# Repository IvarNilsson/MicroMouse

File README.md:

# MicroMouse

Motors and wheels:

Motorcontroller curcuit?

Motor electrokit:
[motor 1](ttps://www.electrokit.com/produkt/dc-motor-med-kuggvaxel-12vdc-301-900rpm-med-enkoder)
[Wheels 1](ttps://www.banggood.com/4PCS-SG-1603-1604-UDIRC-1601-RC-Car-Spare-Tires-Wheels-1603-005-B-Vehicles-Model-Parts-p-1832852.html?utm_source=googleshopping&utm_medium=cpc_organic&gmcCountry=SE&utm_content=minha&utm_campaign=aceng-pmax-se-en-pc&currency=SEK&cur_warehouse=CN&createTmp=1&utm_source=googleshopping&utm_medium=cpc_pt&utm_content=meruem&utm_campaign=aceng-pmax-se-all-en-220402-meruem&ad_id=&gclid=Cj0KCQjw4bipBhCyARIsAFsieCzhoUDw4CZ-vSHbWPWbA6zzIRrXuiuE_EPyn2XLgKM-56ahdmfMtzMaAotqEALw_wc)

Links:
[Tutorial](https://micromouseguideforbeginners.wordpress.com/3-part-1-motorswheels-2/)
[Pololu stuff](https://www.pololu.com/product/3081)
[Pololu stuff](https://www.pololu.com/product/713)
[wheels example](https://micromouseonline.com/2012/05/24/printed-wheels-complete-decimus-mechanicals/)
[cool ideal motor](https://www.glockenankermotor.com/en/dc-micromotors-faulhaber/1717...sr-faulhaber/328/faulhaber-motor-1717t006sr)
[Wheels 2](https://www.banggood.com/4PCS-SG-1603-1604-UDIRC-1601-RC-Car-Spare-Tires-Wheels-1603-005-A-Vehicles-Model-Parts-p-1832874.html?utm_source=googleshopping&utm_medium=cpc_pt&gmcCountry=SE&utm_content=meruem&utm_campaign=aceng-pmax-se-all-en-220402-meruem&currency=SEK&cur_warehouse=CN&createTmp=1&ad_id)

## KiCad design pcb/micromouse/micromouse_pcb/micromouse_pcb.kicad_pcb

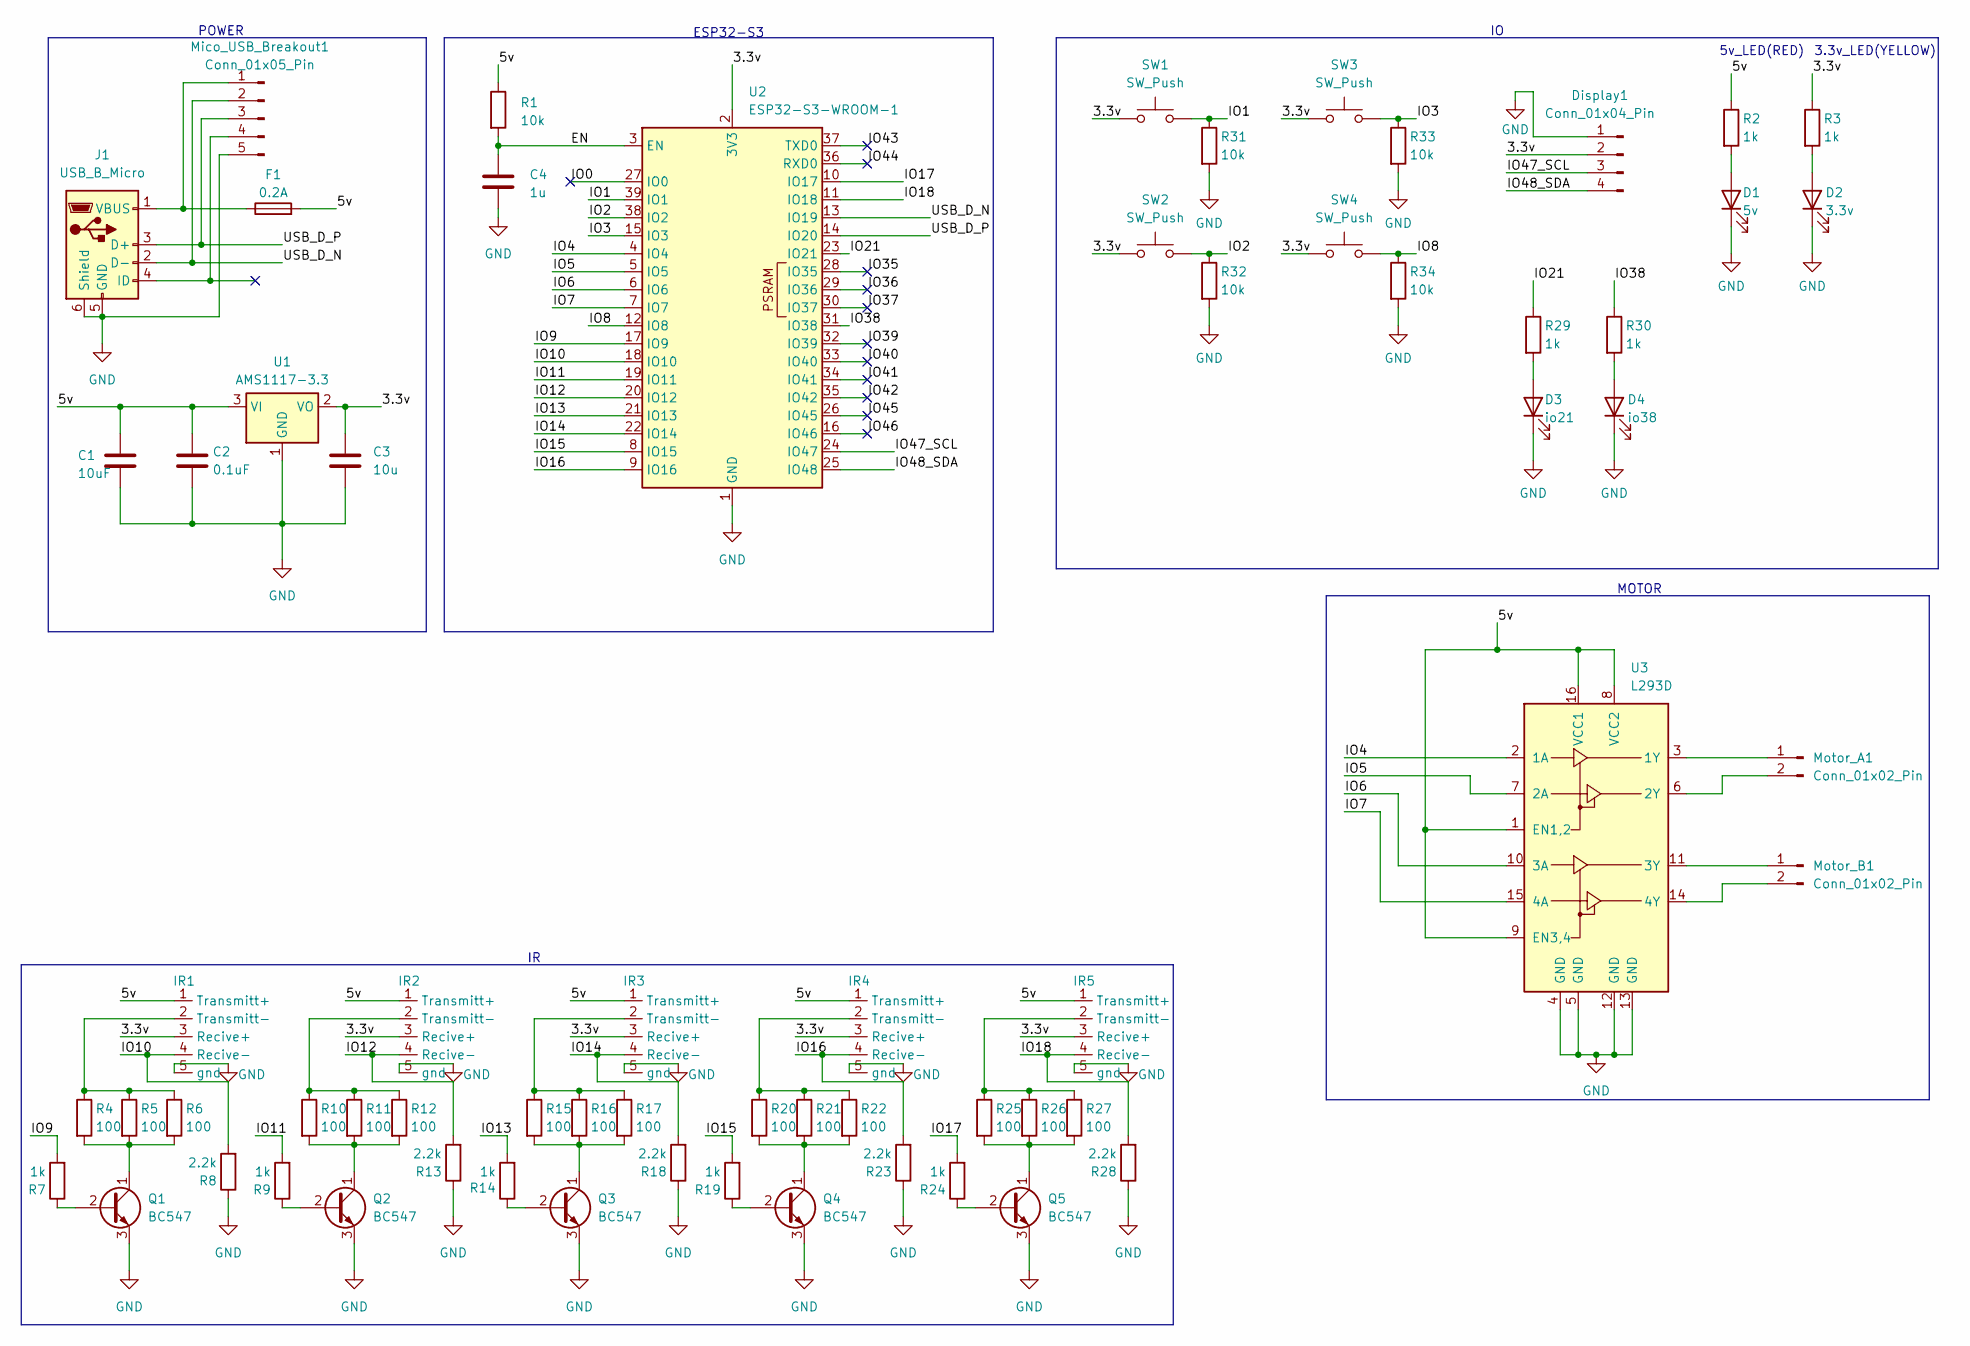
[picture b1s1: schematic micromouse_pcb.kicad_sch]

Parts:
C1: 10uF; IVAR_1206_SMD_C
C2: 0.1uF; IVAR_1206_SMD_C
C3: 10u; IVAR_1206_SMD_C
C4: 1u; IVAR_1206_SMD_C
D1: 5v; IVAR_0603_SMD_LED
D2: 3.3v; IVAR_0603_SMD_LED
D3: io21; IVAR_0603_SMD_LED
D4: io38; IVAR_0603_SMD_LED
Display1: Conn_01x04_Pin; IVAR_OLED_I2C
F1: 0.2A; IVAR_1206_SMD_FUSE
IR1, IR2, IR3, IR4, IR5: IVAR_IR
J1: USB_B_Micro; USB_Micro-B_Amphenol_10103594-0001LF_Horizontal
Mico_USB_Breakout1: Conn_01x05_Pin; IVAR_Micro_USB_breakout_board_5pin
Motor_A1: Conn_01x02_Pin; PinHeader_1x02_P2.54mm_Vertical
Motor_B1: Conn_01x02_Pin; PinHeader_1x02_P2.54mm_Vertical
Q1, Q2, Q3, Q4, Q5: BC547; TO-92_Inline
R1, R31, R32, R33, R34: 10k; IVAR_1206_SMD_R
R2, R3, R7, R9, R14, R19, R24, R29, R30: 1k; IVAR_1206_SMD_R
R4, R5, R6, R10, R11, R12, R15, R16, R17, R20, R21, R22, R25, R26, R27: 100; IVAR_1206_SMD_R
R8, R13, R18, R23, R28: 2.2k; IVAR_1206_SMD_R
SW1, SW2, SW3, SW4: SW_Push; IVAR_BUTTON_RED_SMD
U1: AMS1117-3.3; SOT-223-3_TabPin2
U2: ESP32-S3-WROOM-1
U3: L293D; DIP-16_W7.62mm

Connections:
/3.3v: C3.1, Display1.2, IR1.3 (Recive+), IR2.3 (Recive+), IR3.3 (Recive+), IR4.3 (Recive+), IR5.3 (Recive+), R3.1, SW1.1, SW2.1, SW3.1, SW4.1, U1.2 (VO), U2.2 (3V3)
/5v: C1.1, C2.1, F1.2, IR1.1 (Transmitt+), IR2.1 (Transmitt+), IR3.1 (Transmitt+), IR4.1 (Transmitt+), IR5.1 (Transmitt+), R1.1, R2.1, U1.3 (VI), U3.1 (EN1,2), U3.8 (VCC2), U3.9 (EN3,4), U3.16 (VCC1)
/EN: C4.1, R1.2, U2.3 (EN)
/IO0: U2.27 (IO0)
/IO1: R31.1, SW1.2, U2.39 (IO1)
/IO2: R32.1, SW2.2, U2.38 (IO2)
/IO3: R33.1, SW3.2, U2.15 (IO3)
/IO4: U2.4 (IO4), U3.2 (1A)
/IO5: U2.5 (IO5), U3.7 (2A)
/IO6: U2.6 (IO6), U3.10 (3A)
/IO7: U2.7 (IO7), U3.15 (4A)
/IO8: R34.1, SW4.2, U2.12 (IO8)
/IO9: R7.2, U2.17 (IO9)
/IO10: IR1.4 (Recive-), R8.2, U2.18 (IO10)
/IO11: R9.2, U2.19 (IO11)
/IO12: IR2.4 (Recive-), R13.2, U2.20 (IO12)
/IO13: R14.2, U2.21 (IO13)
/IO14: IR3.4 (Recive-), R18.2, U2.22 (IO14)
/IO15: R19.2, U2.8 (IO15)
/IO16: IR4.4 (Recive-), R23.2, U2.9 (IO16)
/IO17: R24.2, U2.10 (IO17)
/IO18: IR5.4 (Recive-), R28.2, U2.11 (IO18)
/IO21: R29.1, U2.23 (IO21)
/IO35: U2.28 (IO35)
/IO36: U2.29 (IO36)
/IO37: U2.30 (IO37)
/IO38: R30.1, U2.31 (IO38)
/IO39: U2.32 (IO39)
/IO40: U2.33 (IO40)
/IO41: U2.34 (IO41)
/IO42: U2.35 (IO42)
/IO43: U2.37 (TXD0)
/IO44: U2.36 (RXD0)
/IO45: U2.26 (IO45)
/IO46: U2.16 (IO46)
/IO47_SCL: Display1.3, U2.24 (IO47)
/IO48_SDA: Display1.4, U2.25 (IO48)
/USB_D_N: J1.2 (D-), Mico_USB_Breakout1.2, U2.13 (IO19)
/USB_D_P: J1.3 (D+), Mico_USB_Breakout1.3, U2.14 (IO20)
GND: C1.2, C2.2, C3.2, C4.2, D1.1 (K), D2.1 (K), D3.1 (K), D4.1 (K), Display1.1, IR1.5 (gnd), IR2.5 (gnd), IR3.5 (gnd), IR4.5 (gnd), IR5.5 (gnd), J1.5 (GND), J1.6 (Shield), Mico_USB_Breakout1.5, Q1.3 (E), Q2.3 (E), Q3.3 (E), Q4.3 (E), Q5.3 (E), R8.1, R13.1, R18.1, R23.1, R28.1, R31.2, R32.2, R33.2, R34.2, U1.1 (GND), U2.1 (GND), U2.40 (GND), U2.41 (GND), U3.4 (GND), U3.5 (GND), U3.12 (GND), U3.13 (GND)
unnamed: D1.2 (A), R2.2
unnamed: D2.2 (A), R3.2
unnamed: D3.2 (A), R29.2
unnamed: D4.2 (A), R30.2
unnamed: IR1.2 (Transmitt-), R4.1, R5.1, R6.1
unnamed: IR2.2 (Transmitt-), R10.1, R11.1, R12.1
unnamed: IR3.2 (Transmitt-), R15.1, R16.1, R17.1
unnamed: IR4.2 (Transmitt-), R20.1, R21.1, R22.1
unnamed: IR5.2 (Transmitt-), R25.1, R26.1, R27.1
unnamed: F1.1, J1.1 (VBUS), Mico_USB_Breakout1.1
unnamed 50: Motor_A1.1, U3.3 (1Y); also elsewhere on the board
unnamed 51: Motor_A1.2, U3.6 (2Y); also elsewhere on the board
unnamed 52: Motor_B1.1, U3.11 (3Y); also elsewhere on the board
unnamed 53: Motor_B1.2, U3.14 (4Y); also elsewhere on the board
unnamed: Q1.2 (B), R7.1
unnamed: Q1.1 (C), R4.2, R5.2, R6.2
unnamed: Q2.2 (B), R9.1
unnamed: Q2.1 (C), R10.2, R11.2, R12.2
unnamed: Q3.2 (B), R14.1
unnamed: Q3.1 (C), R15.2, R16.2, R17.2
unnamed: Q4.2 (B), R19.1
unnamed: Q4.1 (C), R20.2, R21.2, R22.2
unnamed: Q5.2 (B), R24.1
unnamed: Q5.1 (C), R25.2, R26.2, R27.2

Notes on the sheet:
5v_LED(RED)
POWER
3.3v_LED(YELLOW)
MOTOR
ESP32-S3

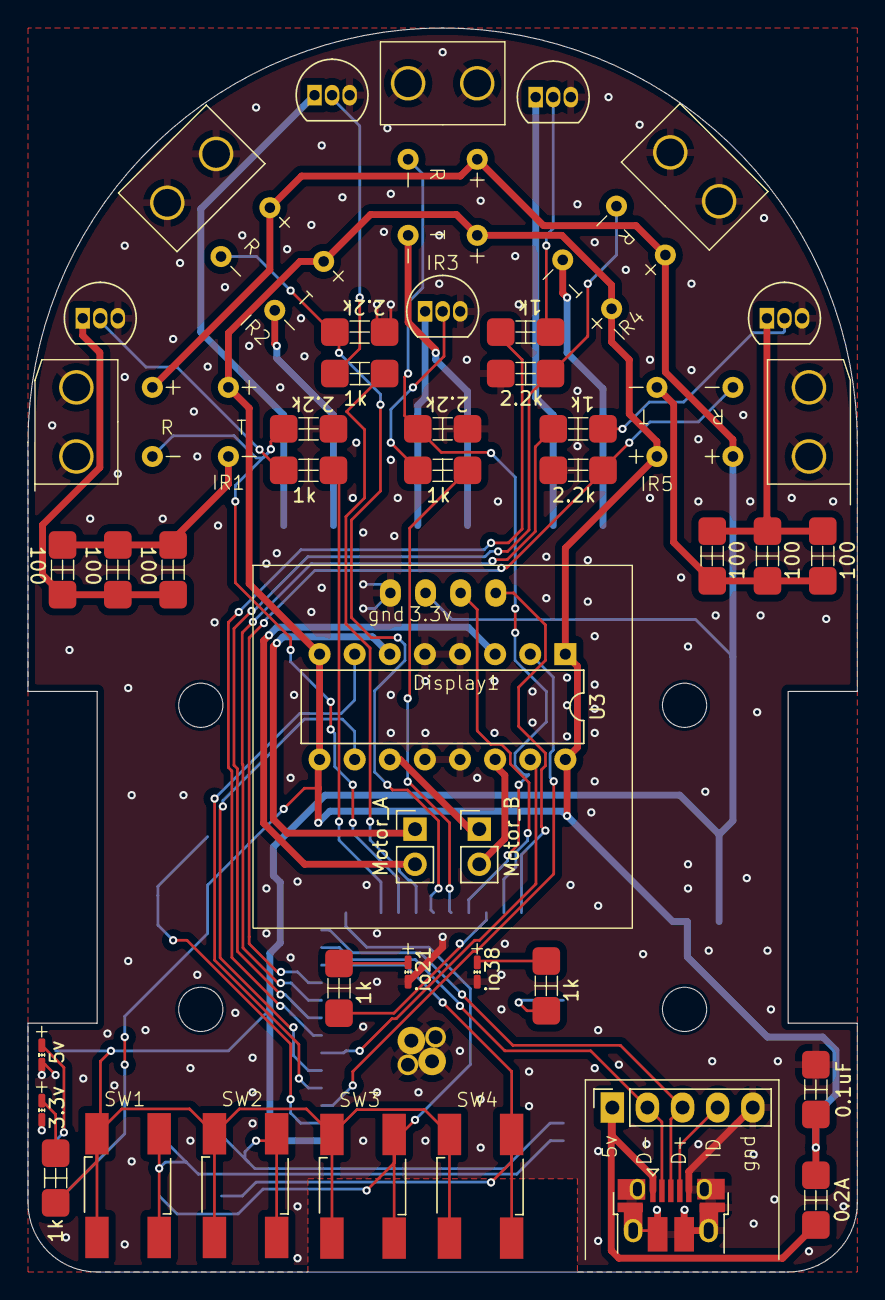
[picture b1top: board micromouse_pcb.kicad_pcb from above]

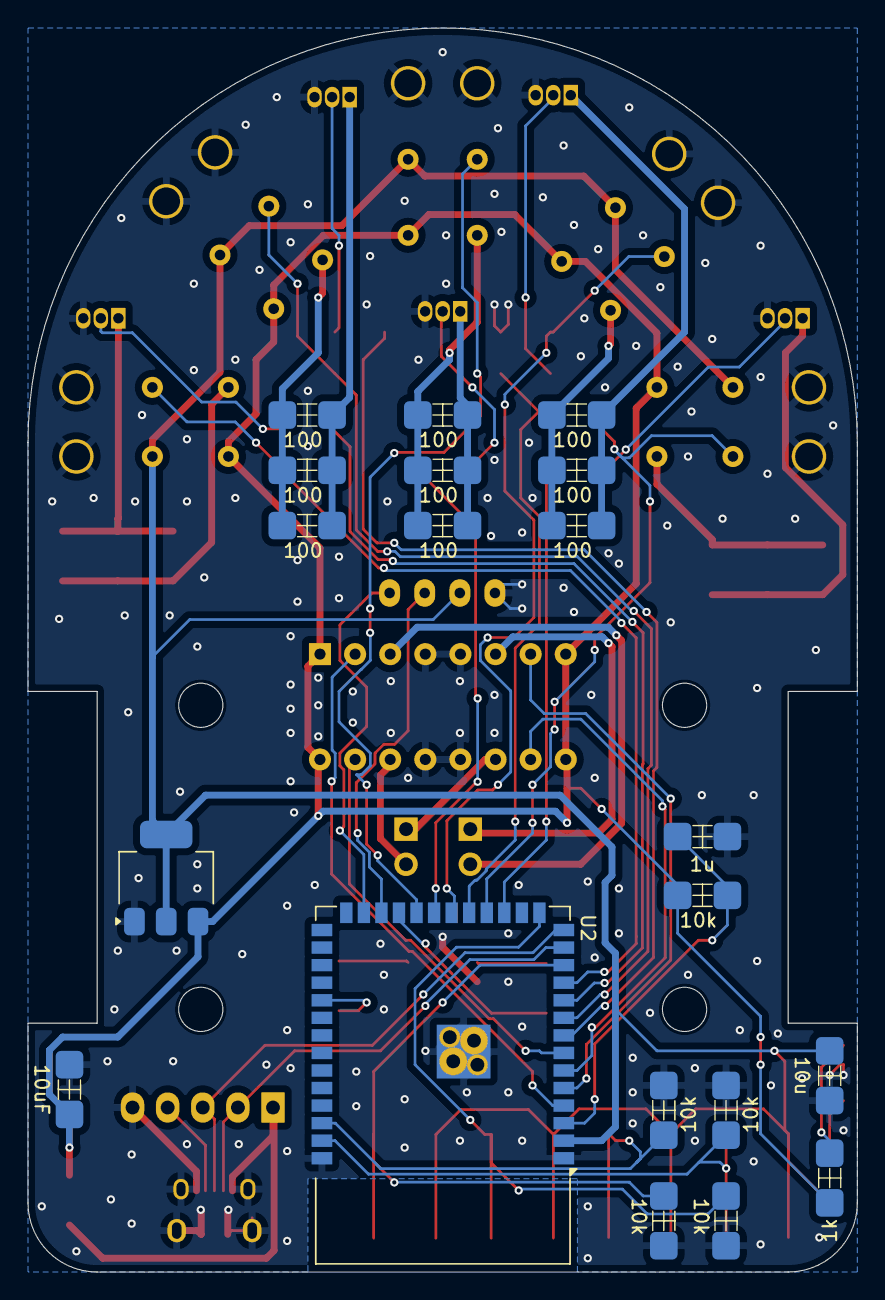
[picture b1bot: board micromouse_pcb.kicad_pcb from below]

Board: 2 copper layers, 60.0 x 90.0 mm, 65 parts (20 on the bottom side), 52 nets.

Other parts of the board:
Motor_A: Conn_01x02_Pin; PinHeader_1x02_P2.54mm_Vertical
Motor_B: Conn_01x02_Pin; PinHeader_1x02_P2.54mm_Vertical

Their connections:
unnamed 50: Motor_A.1; also elsewhere on the board
unnamed 51: Motor_A.2; also elsewhere on the board
unnamed 52: Motor_B.1; also elsewhere on the board
unnamed 53: Motor_B.2; also elsewhere on the board

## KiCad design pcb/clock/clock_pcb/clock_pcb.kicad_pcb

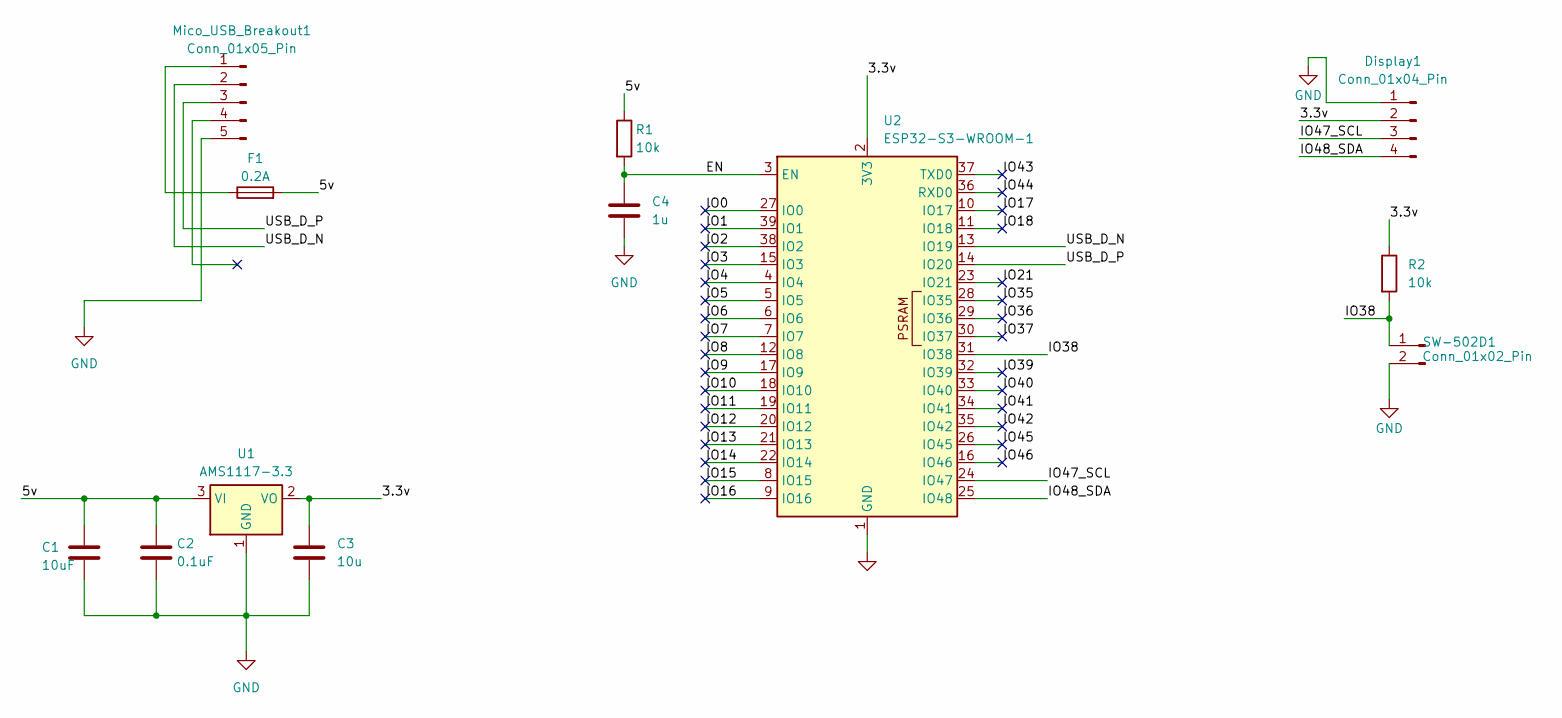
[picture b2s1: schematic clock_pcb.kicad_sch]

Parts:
C1: 10uF; IVAR_1206_SMD_C
C2: 0.1uF; IVAR_1206_SMD_C
C3: 10u; IVAR_1206_SMD_C
C4: 1u; IVAR_1206_SMD_C
Display1: Conn_01x04_Pin; IVAR_OLED_I2C
F1: 0.2A; IVAR_1206_SMD_FUSE
Mico_USB_Breakout1: Conn_01x05_Pin; IVAR_Micro_USB_breakout_board_5pin
R1, R2: 10k; IVAR_1206_SMD_R
SW-502D1: Conn_01x02_Pin; IVAR_MOTION_SENS
U1: AMS1117-3.3; SOT-223-3_TabPin2
U2: ESP32-S3-WROOM-1

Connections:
/3.3v: C3.1, Display1.2, R2.1, U1.2 (VO), U2.2 (3V3)
/5v: C1.1, C2.1, F1.2, R1.1, U1.3 (VI)
/EN: C4.1, R1.2, U2.3 (EN)
/IO0: U2.27 (IO0)
/IO1: U2.39 (IO1)
/IO2: U2.38 (IO2)
/IO3: U2.15 (IO3)
/IO4: U2.4 (IO4)
/IO5: U2.5 (IO5)
/IO6: U2.6 (IO6)
/IO7: U2.7 (IO7)
/IO8: U2.12 (IO8)
/IO9: U2.17 (IO9)
/IO10: U2.18 (IO10)
/IO11: U2.19 (IO11)
/IO12: U2.20 (IO12)
/IO13: U2.21 (IO13)
/IO14: U2.22 (IO14)
/IO15: U2.8 (IO15)
/IO16: U2.9 (IO16)
/IO17: U2.10 (IO17)
/IO18: U2.11 (IO18)
/IO21: U2.23 (IO21)
/IO35: U2.28 (IO35)
/IO36: U2.29 (IO36)
/IO37: U2.30 (IO37)
/IO38: R2.2, SW-502D1.1, U2.31 (IO38)
/IO39: U2.32 (IO39)
/IO40: U2.33 (IO40)
/IO41: U2.34 (IO41)
/IO42: U2.35 (IO42)
/IO43: U2.37 (TXD0)
/IO44: U2.36 (RXD0)
/IO45: U2.26 (IO45)
/IO46: U2.16 (IO46)
/IO47_SCL: Display1.3, U2.24 (IO47)
/IO48_SDA: Display1.4, U2.25 (IO48)
/USB_D_N: Mico_USB_Breakout1.2, U2.13 (IO19)
/USB_D_P: Mico_USB_Breakout1.3, U2.14 (IO20)
GND: C1.2, C2.2, C3.2, C4.2, Display1.1, Mico_USB_Breakout1.5, SW-502D1.2, U1.1 (GND), U2.1 (GND), U2.40 (GND), U2.41 (GND)
unnamed: F1.1, Mico_USB_Breakout1.1

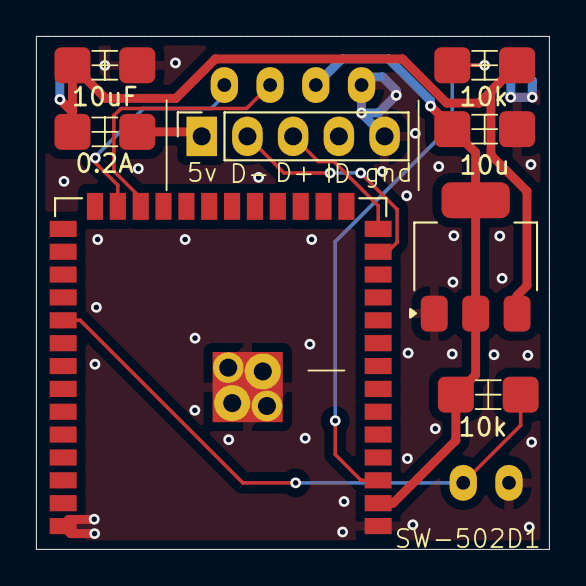
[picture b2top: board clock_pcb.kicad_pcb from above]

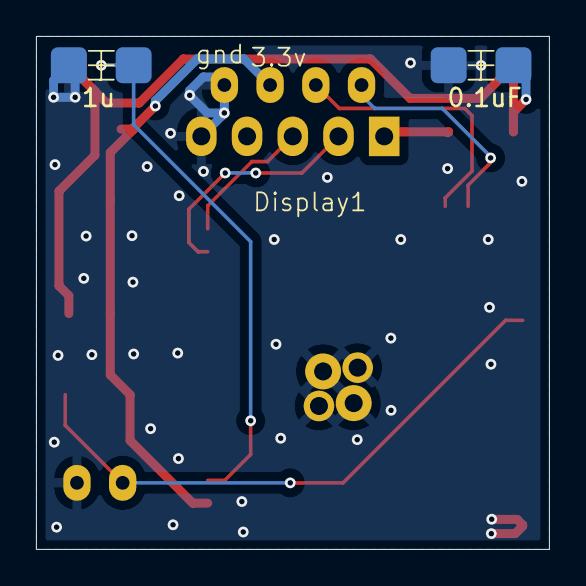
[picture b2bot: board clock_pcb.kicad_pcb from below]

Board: 2 copper layers, 28.5 x 28.5 mm, 12 parts (3 on the bottom side), 10 nets.

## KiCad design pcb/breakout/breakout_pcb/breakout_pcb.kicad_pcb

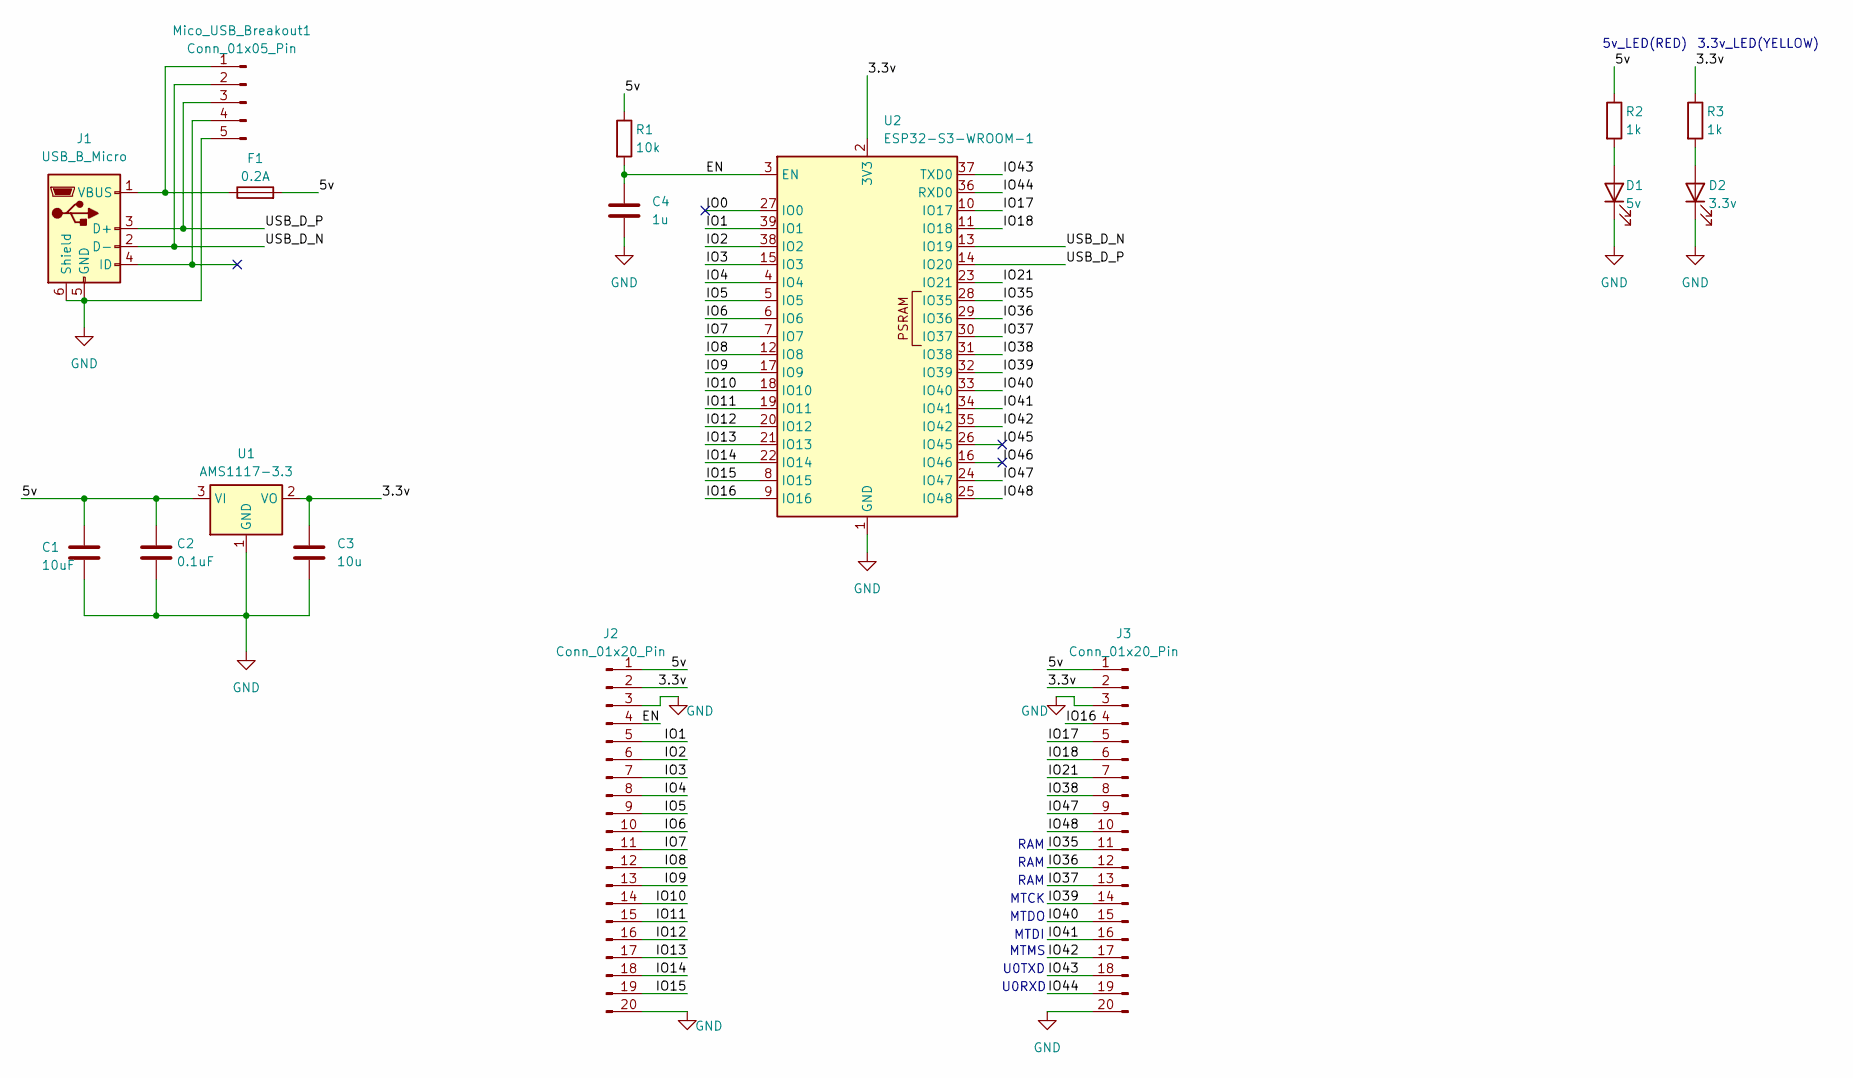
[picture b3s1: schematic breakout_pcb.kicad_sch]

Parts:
C1: 10uF; IVAR_1206_SMD_C
C2: 0.1uF; IVAR_1206_SMD_C
C3: 10u; IVAR_1206_SMD_C
C4: 1u; IVAR_1206_SMD_C
D1: 5v; IVAR_0603_SMD_LED
D2: 3.3v; IVAR_0603_SMD_LED
F1: 0.2A; IVAR_1206_SMD_FUSE
J1: USB_B_Micro; USB_Micro-B_Amphenol_10103594-0001LF_Horizontal
J2, J3: Conn_01x20_Pin; PinHeader_1x20_P2.54mm_Vertical
Mico_USB_Breakout1: Conn_01x05_Pin; IVAR_Micro_USB_breakout_board_5pin
R1: 10k; IVAR_1206_SMD_R
R2, R3: 1k; IVAR_1206_SMD_R
U1: AMS1117-3.3; SOT-223-3_TabPin2
U2: ESP32-S3-WROOM-1

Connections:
/3.3v: C3.1, J2.2, J3.2, R3.1, U1.2 (VO), U2.2 (3V3)
/5v: C1.1, C2.1, F1.2, J2.1, J3.1, R1.1, R2.1, U1.3 (VI)
/EN: C4.1, J2.4, R1.2, U2.3 (EN)
/IO0: U2.27 (IO0)
/IO1: J2.5, U2.39 (IO1)
/IO2: J2.6, U2.38 (IO2)
/IO3: J2.7, U2.15 (IO3)
/IO4: J2.8, U2.4 (IO4)
/IO5: J2.9, U2.5 (IO5)
/IO6: J2.10, U2.6 (IO6)
/IO7: J2.11, U2.7 (IO7)
/IO8: J2.12, U2.12 (IO8)
/IO9: J2.13, U2.17 (IO9)
/IO10: J2.14, U2.18 (IO10)
/IO11: J2.15, U2.19 (IO11)
/IO12: J2.16, U2.20 (IO12)
/IO13: J2.17, U2.21 (IO13)
/IO14: J2.18, U2.22 (IO14)
/IO15: J2.19, U2.8 (IO15)
/IO16: J3.4, U2.9 (IO16)
/IO17: J3.5, U2.10 (IO17)
/IO18: J3.6, U2.11 (IO18)
/IO21: J3.7, U2.23 (IO21)
/IO35: J3.11, U2.28 (IO35)
/IO36: J3.12, U2.29 (IO36)
/IO37: J3.13, U2.30 (IO37)
/IO38: J3.8, U2.31 (IO38)
/IO39: J3.14, U2.32 (IO39)
/IO40: J3.15, U2.33 (IO40)
/IO41: J3.16, U2.34 (IO41)
/IO42: J3.17, U2.35 (IO42)
/IO43: J3.18, U2.37 (TXD0)
/IO44: J3.19, U2.36 (RXD0)
/IO45: U2.26 (IO45)
/IO46: U2.16 (IO46)
/IO47: J3.9, U2.24 (IO47)
/IO48: J3.10, U2.25 (IO48)
/USB_D_N: J1.2 (D-), Mico_USB_Breakout1.2, U2.13 (IO19)
/USB_D_P: J1.3 (D+), Mico_USB_Breakout1.3, U2.14 (IO20)
GND: C1.2, C2.2, C3.2, C4.2, D1.1 (K), D2.1 (K), J1.5 (GND), J1.6 (Shield), J2.3, J2.20, J3.3, J3.20, Mico_USB_Breakout1.5, U1.1 (GND), U2.1 (GND), U2.40 (GND), U2.41 (GND)
unnamed: D1.2 (A), R2.2
unnamed: D2.2 (A), R3.2
unnamed: F1.1, J1.1 (VBUS), Mico_USB_Breakout1.1

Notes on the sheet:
5v_LED(RED)
RAM
MTDO
MTDI
U0TXD
MTCK
3.3v_LED(YELLOW)
MTMS
U0RXD

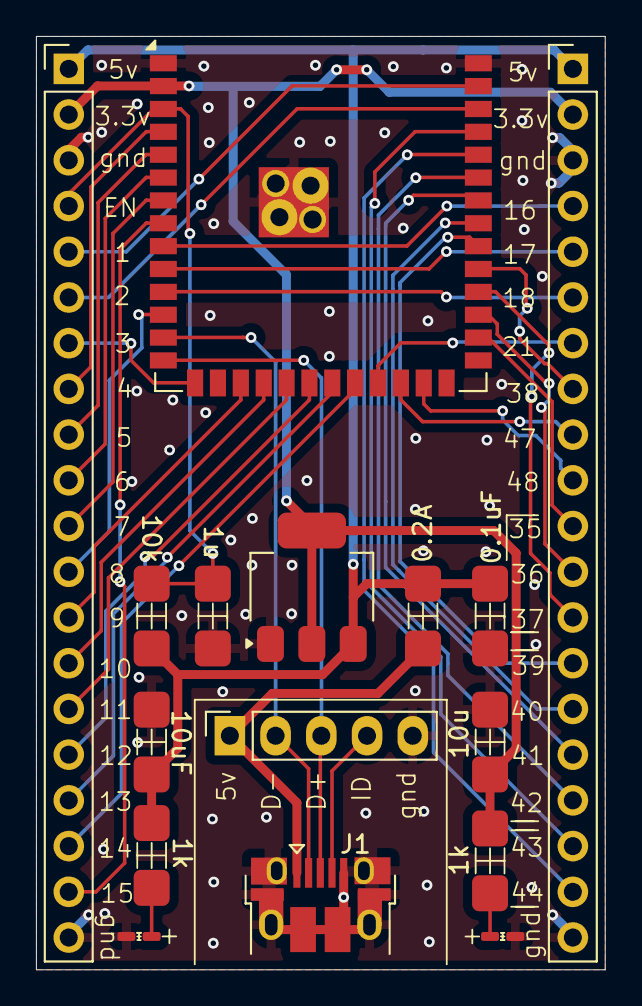
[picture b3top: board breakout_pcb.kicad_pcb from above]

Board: 2 copper layers, 31.6 x 51.8 mm, 16 parts (0 on the bottom side), 40 nets.

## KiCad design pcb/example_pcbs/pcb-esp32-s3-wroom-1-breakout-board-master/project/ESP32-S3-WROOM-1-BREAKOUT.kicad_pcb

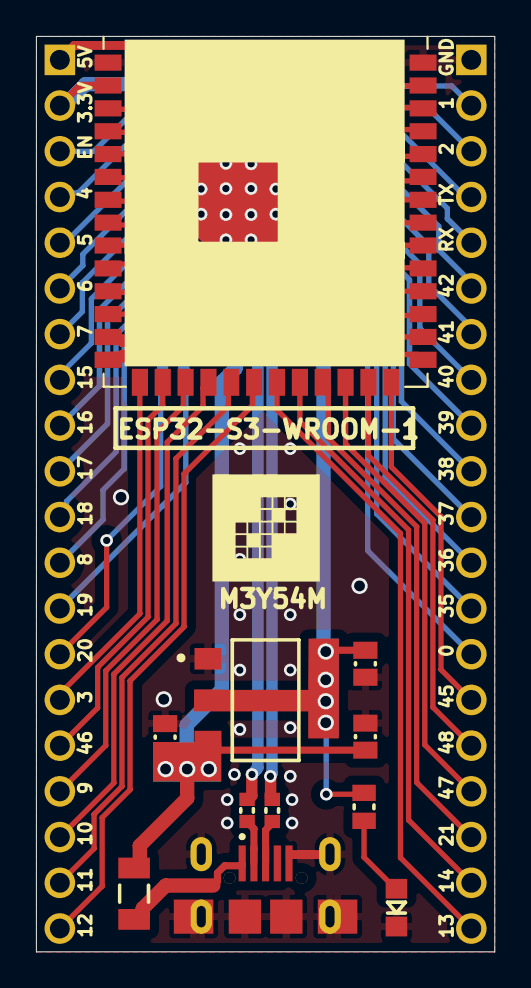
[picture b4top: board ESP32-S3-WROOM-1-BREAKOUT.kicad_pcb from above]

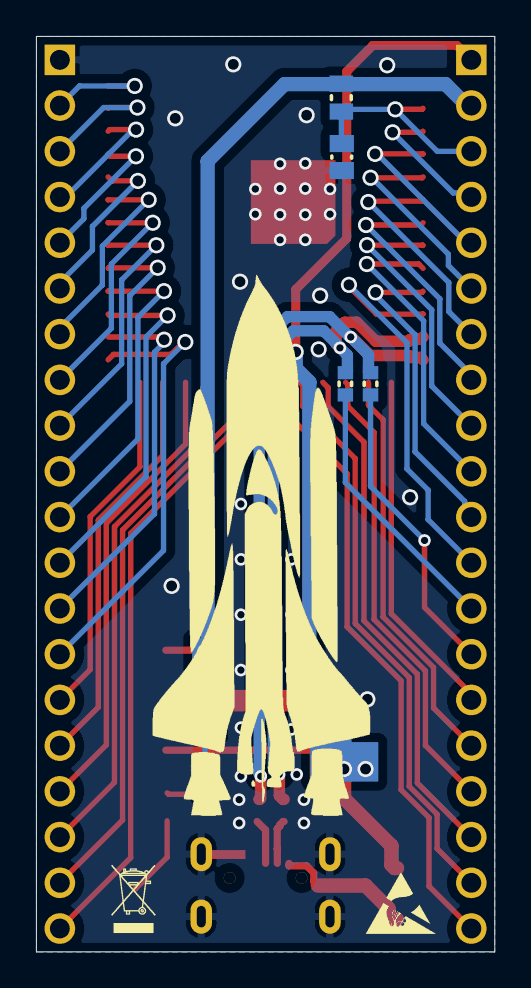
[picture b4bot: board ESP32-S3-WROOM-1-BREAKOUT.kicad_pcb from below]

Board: 2 copper layers, 25.5 x 50.9 mm, 17 parts (4 on the bottom side), 46 nets.

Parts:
C1, C2, C3, C4: C0805C104K5RAC7411; C0805
D1: LED; LED0805
F1: NANOSMDC020F-2; R1206
J1: 629105150921; CON-MICRO-USB-B-SMD-WITH-HOLDER
P1, P2: CON-HDR-1X20; CON-HDR-1X20-2.54
R1, R2, R3, R4: CRG0805F10K; R0603
R5, R6: CRG0805F10K; R0805
U1: ESP32-S3-WROOM-1-N4R2; ESP32-S3-WROOM-1_NO-KEEPOUT
U2: AMS1117-3.3; SOT-223

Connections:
+3V3: C3.1, P1.2, R5.1, R6.2, U1.2, U2.2, U2.4
+5V: C1.1, C2.1, F1.2, P1.1, U2.3
EN: C4.1, P1.3, R6.1, U1.3
GND: C1.2, C2.2, C3.2, C4.2, D1.2, J1.5, J1.Shell, P2.1, U1.1, U1.40, U1.41_1, U1.41_2, U1.41_3, U1.41_4, U1.41_5, U1.41_6, U1.41_7, U1.41_8, U1.41_9, U2.1
GPIO0: P2.14, U1.27
GPIO1: P2.2, U1.39
GPIO2: P2.3, U1.38
GPIO3: P1.15, U1.15
GPIO4: P1.4, U1.4
GPIO5: P1.5, U1.5
GPIO6: P1.6, U1.6
GPIO7: P1.7, U1.7
GPIO8: P1.12, U1.12
GPIO9: P1.17, U1.17
GPIO10: P1.18, U1.18
GPIO11: P1.19, U1.19
GPIO12: P1.20, U1.20
GPIO13: P2.20, U1.21
GPIO14: P2.19, U1.22
GPIO15: P1.8, U1.8
GPIO16: P1.9, U1.9
GPIO17: P1.10, U1.10
GPIO18: P1.11, U1.11
GPIO19: P1.13, R1.1
GPIO20: P1.14, R2.1
GPIO21: P2.18, U1.23
GPIO35: P2.13, U1.28
GPIO36: P2.12, U1.29
GPIO37: P2.11, U1.30
GPIO38: P2.10, U1.31
GPIO39: P2.9, U1.32
GPIO40: P2.8, U1.33
GPIO41: P2.7, U1.34
GPIO42: P2.6, U1.35
GPIO45: P2.15, U1.26
GPIO46: P1.16, U1.16
GPIO47: P2.17, U1.24
GPIO48: P2.16, U1.25
NetD1_1: D1.1, R5.2
NetF1_1: F1.1, J1.1
NetJ1_2: J1.2, R3.2
NetJ1_3: J1.3, R4.2
RXD0: P2.5, U1.36
TXD0: P2.4, U1.37
USB_D_N: R1.2, R3.1, U1.13
USB_D_P: R2.2, R4.1, U1.14

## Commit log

2023-10-17 first_commit
2023-10-28 initial motors and wheels might change later
2023-12-12 new links but project is on hold
2024-09-09 working motor control with L298N
2024-10-21 big commit, started on pcb and much more
2024-10-25 pcb progerss clock and breakout_board done
2024-10-27 subsystem testing complete
2024-10-28 pcb of micromouse done
2024-11-09 pcb on order, started work on a simulator
2024-11-26 testing clock pcb
2024-11-26 merge
2024-12-30 progress on simulator and some fixes
2025-01-20 Big change to the maze simulator it works way better now :)
2025-01-26 added a mosue (square for now) that knows of its surrondings
2025-03-05 The simulated mouse have learnt how to solve a maze! 🐁
